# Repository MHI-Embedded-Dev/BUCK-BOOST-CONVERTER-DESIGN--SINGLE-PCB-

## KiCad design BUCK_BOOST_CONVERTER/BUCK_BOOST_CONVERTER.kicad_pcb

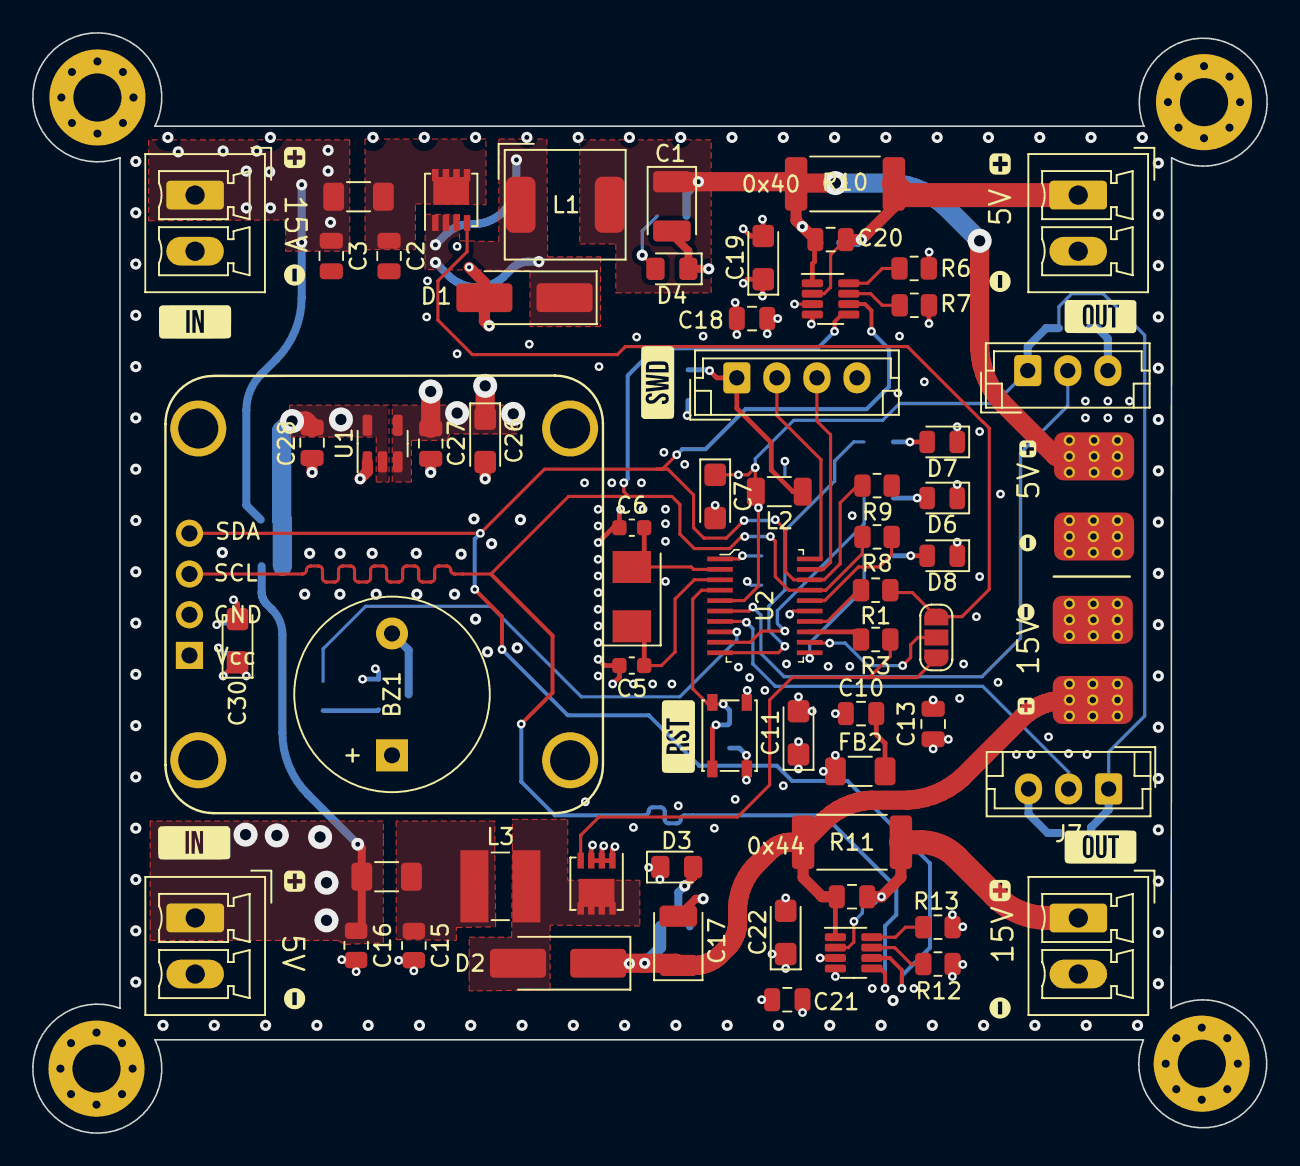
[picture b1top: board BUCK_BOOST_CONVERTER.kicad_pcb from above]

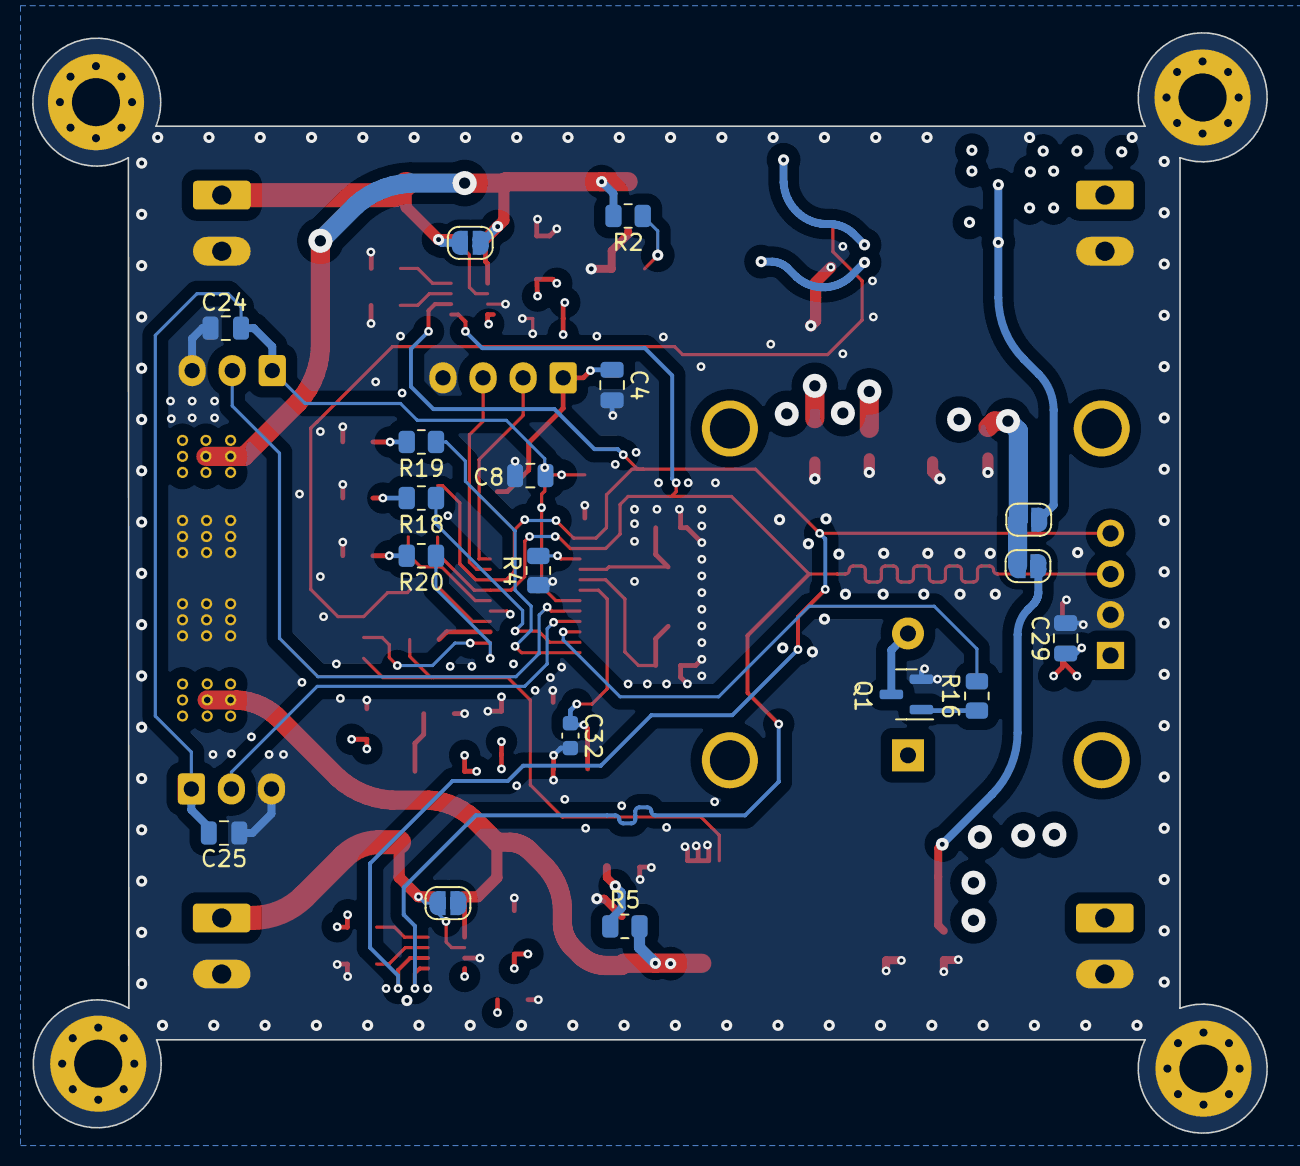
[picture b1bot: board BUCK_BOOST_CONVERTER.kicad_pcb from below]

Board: 4 copper layers, 77.0 x 68.6 mm, 87 parts (18 on the bottom side), 46 nets.

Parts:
A1, A2: INA219; SOT-23-8
B2: RST; SW_SPST_PTS810
BZ1: Buzzer; Buzzer_12x9.5RM7.6
C1: 22uF; CP_EIA-3528-21_Kemet-B
C2: 100nF; C_0805_2012Metric
C3: 4.7uF; C_0805_2012Metric
C4, C8, C10, C13, C18, C20, C21, C23, C24, C25, C27, C28, C29: 100n; C_0805_2012Metric
C5, C6: 10p; C_0603_1608Metric
C7, C11, C19, C22, C26, C30: 2.2uF; CP_EIA-3216-18_Kemet-A
C15: 100nF; R_0805_2012Metric
C16: 4.7uF; R_0805_2012Metric
C17: 1.5uF; CP_EIA-3528-21_Kemet-B
C32: 100n; C_0603_1608Metric
D1, D2: D1FH3; D_SMA_Handsoldering
D3, D4: LED; LED_0805_2012Metric_Pad1.15x1.40mm_HandSolder
D5: SSD1306-OLED; OLED-SSD1306
D6: RED; LED_0805_2012Metric
D7: BLUE; LED_0805_2012Metric
D8: GREEN; LED_0805_2012Metric
FB1, FB2, FB3: 100R; R_1206_3216Metric_Pad1.30x1.75mm_HandSolder
FET1, FET2: Vishay_PowerPAK_1212-8_Single
He1, He2, He3, He4: MountingHole_Pad; MountingHole_3mm_Pad_Via
J1, J3: INPUT; PhoenixContact_MCV_1,5_2-G-3.5_1x02_P3.50mm_Vertical
J2: OUT_BUCK; PhoenixContact_MCV_1,5_2-G-3.5_1x02_P3.50mm_Vertical
J4: TEMP1; JST_EH_B3B-EH-A_1x03_P2.50mm_Vertical
J5: SWD; JST_EH_B4B-EH-A_1x04_P2.50mm_Vertical
J6: OUT_BOOST; PhoenixContact_MCV_1,5_2-G-3.5_1x02_P3.50mm_Vertical
J7: TEMP2; JST_EH_B3B-EH-A_1x03_P2.50mm_Vertical
J8, J9: SMD_PAD; Power_PAD_5A
JP1: Jumper_3_Open; SolderJumper-3_P1.3mm_Open_RoundedPad1.0x1.5mm_NumberLabels
JP2, JP3, JP4, JP5: SolderJumper_2_Open; SolderJumper-2_P1.3mm_Open_RoundedPad1.0x1.5mm
L1: 47uH; L_AVX_LMLP07A7
L2: 500ohm; R_1206_3216Metric
L3: 3.9uH; L_Ferrocore_DLG-0403
Q1: BC846A; SOT-23
R1, R3: 0R; R_0805_2012Metric
R2: 1K; R_0805_2012Metric
R4: 10k; R_0805_2012Metric
R5: 4.7k; R_0805_2012Metric
R6, R7, R8, R9, R12, R13: 2.2k; R_0805_2012Metric
R10: 100R; R_2512_6332Metric_Pad1.40x3.35mm_HandSolder
R11: 1R; R_2512_6332Metric_Pad1.40x3.35mm_HandSolder
R16: 480R; R_0805_2012Metric
R18, R19, R20: 470R; R_0805_2012Metric
U1: TLV70533; SOT-23-5
U2: STM32F030F4P6; TSSOP-20_W4.4mm
Y1: 8MHz; Crystal_SMD_5032-2Pin_5.0x3.2mm

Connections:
15V_BOOST: A2.1 (Vin+), C17.1, C23.1, D2.1 (K), J9.1, JP5.2 (B), R5.2, R11.1
+3.3V: A1.4 (VCC), A2.4 (VCC), BZ1.1 (-), C11.1, C13.1, C18.1, C19.1, C21.1, C22.1, C26.1, C27.1, C29.1, C30.1, D5.1 (VCC), FB2.1, R13.2, U1.3 (OUT), U1.4 (OUT)
+3.3VA: C7.1, C8.1, C24.1, C25.1, J4.1, J7.1, L2.2, U2.5 (VDDA)
+3.3VP: C4.1, J5.1, L2.1, R8.1, R9.1, U2.16 (VDD)
+5V: A1.1 (Vin+), C1.1, C20.1, J8.1, JP2.2 (B), L1.2, R2.2, R10.1
+5VD: C16.1, FB3.1, J3.1, JP4.2 (B)
+15V: C3.1, FB1.1, J1.1, JP3.2 (B)
ADC_1: J4.2, U2.6 (PA0)
ADC_2: J7.2, U2.7 (PA1)
BOOST_PWM: FET2.4 (G), JP1.3 (B), R3.1
BOOT0: R4.2, U2.1 (BOOT0)
BUCK_PWM: FET1.4 (G), JP1.1 (A), R1.2
BUZZER: R16.2, U2.8 (PA2)
GND: A1.3 (GND), A2.3 (GND), B2.2, C1.2, C2.2, C3.2, C4.2, C5.2, C6.2, C7.2, C8.2, C10.2, C11.2, C13.2, C15.2, C16.2, C17.2, C18.2, C19.2, C21.2, C22.2, C24.2, C25.2, C26.2, C27.2, C28.2, C29.2, C30.2, C32.2, D1.2 (A), D3.1 (K), D4.1 (K), D5.2 (GND), D6.1 (K), D7.1 (K), D8.1 (K), FET2.1 (S), FET2.2 (S), FET2.3 (S), He1.1, He2.1, He3.1, He4.1, J1.2, J2.2, J3.2, J4.3, J5.4, J6.2, J7.3, J8.2, J9.2, Q1.2 (E), R4.1, R6.2, R7.2, R12.2, U1.1 (GND), U2.15 (VSS)
I2C1_SCL: A1.5 (SCL), A2.5 (SCL), D5.3 (SCL), R8.2, U2.17 (PA9)
I2C1_SDA: A1.6 (SDA), A2.6 (SDA), D5.4 (SDA), R9.2, U2.18 (PA10)
LED1: R18.1, U2.9 (PA3)
LED2: R19.1, U2.10 (PA4)
LED3: R20.1, U2.11 (PA5)
NRST: B2.1 (2), C32.1, U2.4 (NRST)
unnamed: A1.7 (A0), R7.1
unnamed: A1.8 (A1), R6.1
unnamed: A1.2 (Vin-), C20.2, J2.1, JP2.1 (A), R10.2
unnamed: A2.7 (A0), R12.1
unnamed: A2.8 (A1), R13.1
unnamed: A2.2 (Vin-), C23.2, J6.1, JP5.1 (A), R11.2
unnamed: BZ1.2 (+), Q1.3 (C)
unnamed: C10.1, FB2.2
unnamed: C15.1, FB3.2, L3.1
unnamed: D1.1 (K), FET1.1 (S), FET1.2 (S), FET1.3 (S), L1.1
unnamed: D2.2 (A), FET2.5 (D), L3.2
unnamed: D3.2 (A), R5.1
unnamed: D4.2 (A), R2.1
unnamed: D6.2 (A), R18.2
unnamed: D7.2 (A), R19.2
unnamed: D8.2 (A), R20.2
unnamed: C2.1, FB1.2, FET1.5 (D)
unnamed: C28.1, JP3.1 (A), JP4.1 (A), U1.2 (IN), U1.5 (IN)
unnamed: Q1.1 (B), R16.1
unnamed: R3.2, U2.13 (PA7)
unnamed: R1.1, U2.14 (PB1)
OSC_IN: C5.1, U2.3 (PF1), Y1.1
OSC_OUT: C6.1, U2.2 (PF0), Y1.2
PWM_EXTRA: JP1.2 (C), U2.12 (PA6)
SW_CLK: J5.2, U2.20 (PA14)
SW_DIO: J5.3, U2.19 (PA13)

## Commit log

2024-04-27 Buck ve Boost Converter Tasarımı
    KiCAD programı ile tasarlandı ve gerekli olan hesaplamalar aratırılıp elde edilen denklemler uyulanarak nihai tasarım çıkarılmıştır. Sistem özellikleri linkedin gönderimde mecvuttur.
    https://www.linkedin.com/feed/update/urn:li:activity:7189669564903813120/
